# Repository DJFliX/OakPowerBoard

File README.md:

# OakPowerBoard
A Power Consumption board using the TCRT5000 to count pulses. The board is intended as a shield for DigiStump's Oak board. Check it out [here](http://digistump.com/oak/)!

##How does it look?
Great question, I've made screenshots of the board I sent to OSH-Park:

##Is the code finished?
I've made some progress on the code, but unfortunately to test the real sensor I'll have to wait until the board from oshpark arrive. For now, I'm simulating the pulse meter with a button. Below you can find a list of features that are already implemented as well as features that will be implemented in the near future.

Done:
- [X] Show (& calc) total consumption
- [X] Use interrupts to get button input + pulses
- [X] Use button input to switch between frames
- [X] Persistent storage of KWh counter

Future wishes:
- [ ] Add NTP time to sketch
- [ ] Implement timezone offset, apply to current time
- [ ] Keep track of total consumption for the day (and display this)
- [ ] Create some kind of menu for settings
- [ ] Set counter starting position
- [ ] Send consumption to some kind of server?
- [ ] Calibration of pulse detection?
- [ ] Multi-SSID
- [ ] Store measurements while there is no Wi-Fi connection
- [ ] Work stand-alone (without Wi-Fi connection) without switching to Config mode
- [ ] Reduce Flash memory wear by writing periodically instead of on every KWh increment

##Resources used
* [SparkFun Eagle Libraries](https://github.com/sparkfun/SparkFun-Eagle-Libraries) by [SparkFun](https://github.com/sparkfun)
* [TCRT5000 Eagle Library](https://github.com/mohamedpsx/Eagle-Libraries) by [mohamedpsx](https://github.com/mohamedpsx)

* [esp8266-oled-ssd1306](https://github.com/squix78/esp8266-oled-ssd1306) by [squix78](https://github.com/squix78))
* [EEPROMWriteAnything](http://playground.arduino.cc/Code/EEPROMWriteAnything) by the Arduino Community

* [AirSensor Energy Monitor tutorial](http://www.airsensor.co.uk/component/zoo/item/energy-monitor.html)
* [nongnu.org dtostrf](http://www.nongnu.org/avr-libc/user-manual/group__avr__stdlib.html#ga060c998e77fb5fc0d3168b3ce8771d42)
* [SSD1306 Tools Font Converter](http://oleddisplay.squix.ch)

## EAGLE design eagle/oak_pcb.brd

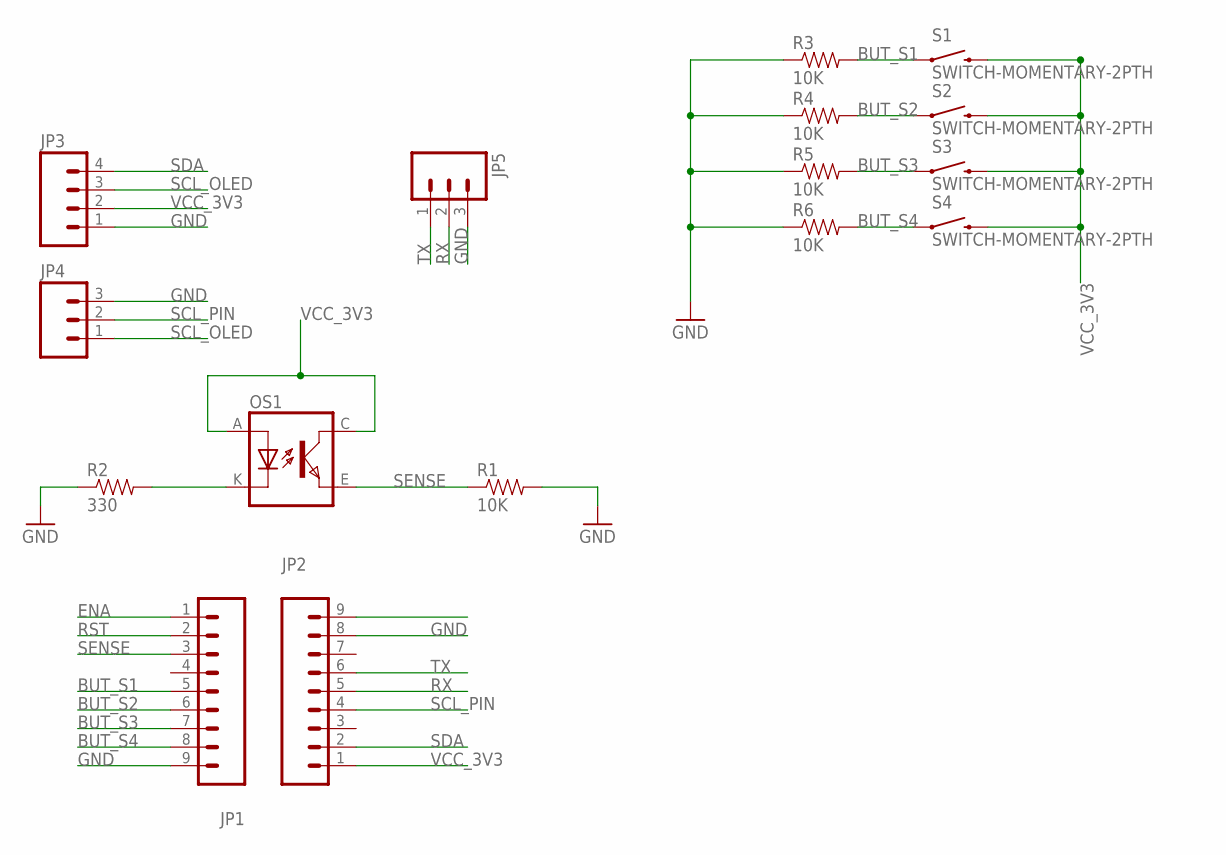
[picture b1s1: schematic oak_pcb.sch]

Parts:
JP1, JP2: M09LOCK; 1X09_LOCK
JP3: M04LOCK; 1X04_LOCK
JP4, JP5: M03LOCK; 1X03_LOCK
OS1: TCRT5000
R1, R3, R4, R5, R6: 10K; AXIAL-0.4
R2: 330; AXIAL-0.4
S1, S2, S3, S4: SWITCH-MOMENTARY-2PTH; TACTILE-PTH

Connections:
BUT_S1: JP1.5, R3.P$2 (2), S1.1
BUT_S2: JP1.6, R4.P$2 (2), S2.1
BUT_S3: JP1.7, R5.P$2 (2), S3.1
BUT_S4: JP1.8, R6.P$2 (2), S4.1
ENA: JP1.1
GND: JP1.9, JP2.8, JP3.1, JP4.3, JP5.3, R1.P$2 (2), R2.P$1 (1), R3.P$1 (1), R4.P$1 (1), R5.P$1 (1), R6.P$1 (1)
unnamed: OS1.K (CATHODE), R2.P$2 (2)
RST: JP1.2
RX: JP2.5, JP5.2
SCL_OLED: JP3.3, JP4.1
SCL_PIN: JP2.4, JP4.2
SDA: JP2.2, JP3.4
SENSE: JP1.3, OS1.E (EMITTER), R1.P$1 (1)
TX: JP2.6, JP5.1
VCC_3V3: JP2.1, JP3.2, OS1.A (ANODE), OS1.C (COLLECTOR), S1.3 (2), S2.3 (2), S3.3 (2), S4.3 (2)

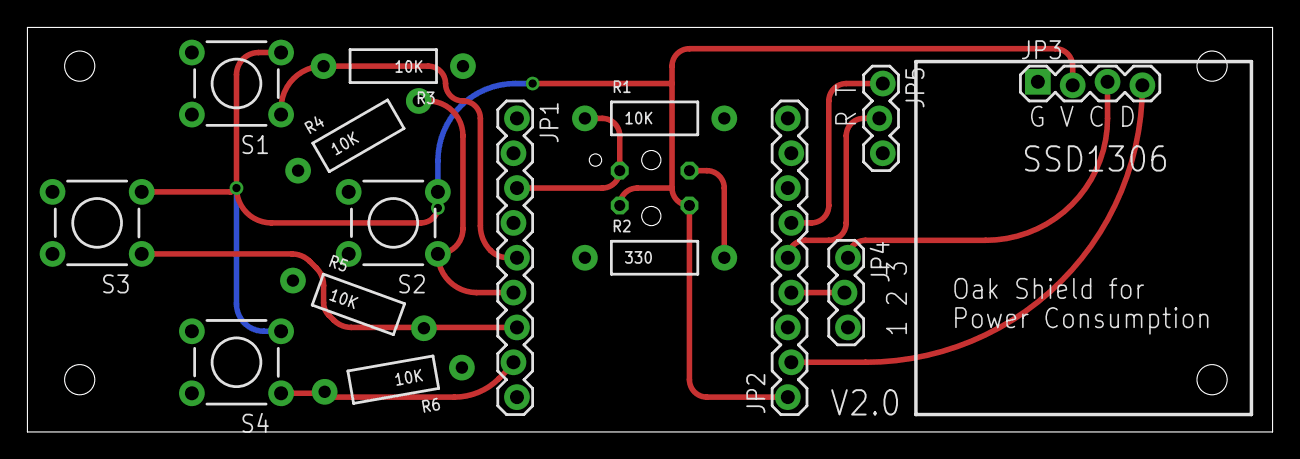
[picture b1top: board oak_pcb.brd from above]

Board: 2 copper layers, 90.8 x 29.5 mm, 16 parts (1 on the bottom side), 13 nets.

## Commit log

2016-02-03 Added Board Files
2016-02-03 Update readme and add board image from oshpark.
2016-02-04 Moved eagle files and modified Readme.md
2016-02-04 Add empty sketch and some resources
2016-02-04 Add the display loop
    Added three frames that are displayed. The current frames are: total
    power consumption (KWh), current consumption (W), and consumption today
    (KWh). Of course, data is static.
2016-02-04 Added initial pulse calculation and string conversion
    When a pulse is detected (currently emulated using a button) the
    current power consumption is calculated and displayed on the screen.
    The value for “Current (W)” is now actually based on the float value.
    Total is based on the float value, but is not updated properly. Today
    is not implemented yet, as we don’t have time yet.
2016-02-07 Corrected current consumption calculation formula.
2016-02-07 Fixed calculation of total KWH
2016-02-07 Removed unnecessary negative if statement
2016-02-07 Move fonts to subdirectory
2016-02-07 Move implementations below loop function()
2016-02-07 Delay with the remaining budget after measuring pulse instead
    Also: comment these lines out because apparently a delay is a problem.
2016-02-09 Removed the frame that we don't use (consumption today)
2016-02-09 Oops... forgot to commit the changes concerning the not-so-dynamic number of frames and overlays...
2016-02-09 Replace the digitalRead with interrupt-based triggers.
2016-02-09 Increase the display time per frame
2016-02-09 And of course, a Pulse trigger also has to be handled...
2016-02-09 Move the yield to yield only if we have a sufficient remainingTimeBudget
2016-02-10 Added persistent storage! Every KWH the counter is stored.
    Will change to a regular interval later on to reduce flash memory wear.
2016-02-16 Move fonts to root, apparently Arduino 1.6.5 does not like subfolders.
    Strangely enough, it worked on 1.6.7… But that version had other issues.
2016-02-16 Move EEPROM include
2016-02-16 Added extra yields to lower the WiFi congestion during the loop
    Also fixed an ugly bug that made the loop delay forever.
2016-02-16 Add Particle Cloud variable to read KWh meter remotely
2016-02-17 Board update, fixed some unfortunate mistakes on my part.
    The oak only has a single Analog pin, I attached the sensor to one of
    the digital pins. I can bodge the existing boards, but I’ve chosen to
    order new boards anyway. So this will be version 2.0, also containing a
    Ground pin for the UART connection as well as bigger holes for the IR
    sensor and a jumper to set the module in ‘bootloader’ mode.
2016-02-17 Update pin definition because of design bodge.
2016-02-17 Only initialise DEBUG_LED if DEBUG is set
2016-02-17 Added analog counter to test with actual Kwh counter
    The value that is measured is displayed as an overlay
2016-02-17 Added a Menu Frame (for further development).
2016-02-17 Remove interrupt (because we can't use that anymore :( )
2016-02-17 Fix typo that made the code run incorrectly.
2016-02-17 Added a Calibration frame that displays the current analogRead value
    Also displays some static values for high and low. As a tease.
2016-02-24 Put the character arrays in a struct to structure the code a little more.
    Also added a High/Low/Current display in the “calibration menu” thingie.
2016-03-09 Add web server content
2016-03-12 Fix crashes if the deadline >= millis()
2016-03-12 Change debug pin to on-board LED
2016-03-12 Include web content and initial support for CDN-hosted content
2016-03-12 Add Bootstrap CDN example
2016-03-12 Added http Get function to CDN JS to bootstrap our control panel.
    Also added implementation of the API functions for buttons :)
2016-03-12 Update web content to include bc div.
2016-03-12 Move web button handlers to a separate file
2016-03-12 Extract some implementations from the .ino and stored them in separate .h files.
2016-03-12 Added Bootstrap and bootstrappy buttons :)
2016-03-12 Fix stupid typo/mistake in naming of the css element to add
2016-03-12 Changed array of objects to string array with button glyphs
2016-03-12 Use different method of assigning class to span
2016-03-12 Also do this for the Input element
2016-03-12 Fixed loading Glyphs by changing the element type of the buttons. Also fix 0-based indexing for glyph index
2016-03-12 Remove global buffer
2016-03-12 Add status handler to API
2016-03-12 Start creating a KWH input field that is populated with the latest value from EEPROM
2016-03-12 Oops... made a mistake in callback format
2016-03-12 Increase buffer size and fix status parsing for api/status
2016-03-12 Move button handlers to a separate file
2016-03-12 Added mDNS/bonjour advertising (advertising as oakpb.local)
2016-03-13 Remove unused web content and added code to retrieve unix timestamp from the interwebs.
2016-03-13 Wrap strings with F to reduce global memory usage
2016-03-13 Add variable so we can run the JavaScript locally and still use the // scheme on-line :)

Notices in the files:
parts and their libraries:
SparkFun-Connectors: Licensing: Creative Commons ShareAlike 4.0 International - https://creativecommons.org/licenses/by-sa/4.0
